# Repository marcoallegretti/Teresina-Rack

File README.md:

# Teresina-Rack

**Version 0.1.0-alpha0 — under engineering review; not fabricated or hardware-tested.** The current PCB is a 12-layer baseline with confirmed electrical, BOM, package and layout findings. It is not approved for production.

The goal is an open, self-fabricatable Daisy Patch SM-compatible Eurorack submodule: the same carrier interface and libDaisy application compatibility through a small Teresina firmware variant. Source compatibility and hardware behavior remain qualification targets. See [the firmware policy](docs/firmware-policy.md) and [production review](docs/production-review.md).

| Top | Bottom |
|---|---|
|  |  |

## Production target

**4 copper layers preferred; 6 acceptable if required; 8 the final fallback.** Evaluate in that order with new placement, BGA escape, timing, return-path and manufacturer review. Document the constraint and alternatives tried before increasing layer count. Twelve layers describe the existing file only and are outside the redesign target. See [the redesign plan](docs/redesign-plan.md).

Disposable four-layer MCU escape trials reached zero native clearance errors when six power-pad vias were filled/capped. The full board remains unrouted in those studies, and SDRAM escape at the inherited placement still fails. These results do not qualify a four-layer production design.

## Existing hardware

| Block | Baseline |
|---|---|
| Interface |68 × 40 mm, 40 through-hole mating pads; all 40 local pad geometries match official CAD |
| MCU |STM32H750IBK6, UFBGA176+25 balls, 480 MHz Cortex-M7 |
| RAM |IS42S32160F-6BLI prototype candidate, 64 MB, 3.3 V, 32-bit FMC; requires the Teresina refresh profile and hardware qualification |
| Flash |IS25LP064A, 8 MB QSPI |
| Codec |PCM3060, SAI1, I²C2 address 0x46 |
| Analog |TL074 audio, MCP6004 CV/gates, LM4040-10 V reference |
| Power |TPS62170 digital buck, LD1117 5 V stage; component selection/layout/budgets require correction |
| Files |209 schematic component references, 214 PCB footprints including five fiducials |

Manufacturer pin maps confirm the core/codec/analog signal assignments. 74 checked digital-net assignments agree with pinned libDaisy. Complete carrier fit, sequencing, analog performance and firmware execution still need first-article validation.

## Open compatibility findings

Official libDaisy v9.0.0 is the pinned firmware reference. Its stock refresh sweep is 168.35 ms against the proposed ISSI part's 64 ms requirement. An opt-in Teresina prototype now implements a conservative refresh profile and reviewed clock/init changes. Crossbuilds support a limited source-compatibility claim; stock binaries are unsupported and hardware tests remain unrun. See [the firmware decision](docs/firmware-policy.md) and [original retention check](docs/review/core-review/bounded-acceptance.md).

An [expanded memory-replacement search](docs/memory-replacement-search.md) found no datasheet-backed fix for unchanged firmware. Etron EM63B325BK is an unresolved catalogue lead; it has not been qualified or selected.

The review also confirms wrong ferrite/inductor/capacitor ordering data, crystal/diode footprint mismatches, CV amplifiers on the wrong supply, gate-output resistance differences and remote critical power/clock/decoupling loops. The earlier claims of an identical analog implementation and completed production validation are superseded by [the current findings](docs/production-review.md). Reviewed corrections are staged outside the checkout until the complete design can be synchronized.

## Validation

| Check | Baseline result and boundary |
|---|---|
| Native KiCad 10.0.7 DRC |0 errors, 0 unconnected, 414 warnings |
| Native ERC |3 power-pin conflicts, 250 warnings; unresolved |
| Native netlist→PCB |821 functional pad assignments agree; intentional NC aliases separately checked |
| Connectivity |200 routed nets connected; native zone-refill agreement |
| Copper hygiene |384 candidate findings; requires geometric review |
| SPICE |63 generated tests pass; ideal channel benches also executed; device/rail/tolerance coverage incomplete |
| EMC/thermal |Risk analyses executed; thermal budget incomplete; no compliance measurement |
| Fabrication export |34 Gerbers, PTH/NPTH drills, CPL; baseline only |

A clean native DRC does not resolve wrong ordered parts or prove stock-firmware retention, thermal safety, analog performance or carrier fit. See the full review for passed, failed and unrun checks.

## Development and fabrication

Use KiCad 10 for the project under `TeresinaRack/`. The configured cloud environment retains checksum-verified KiCad 10.0.7, ngspice 47, kicad-tools, KiCadRoutingTools and kicad-happy; reproducible setup/startup instructions are saved in environment settings. Interactive GUI editing and hardware programming were not validated in the headless environment.

Keep every routing operation's before/after evidence and run native DRC/refill, independent connectivity and copper hygiene before accepting it. Use the actual selected JLCPCB process, not an unrelated generic profile. Final fabrication requires an accepted stackup, explicit filled/capped-via process, corrected sourcing-complete BOM, CPL/assembly drawings, header dimensions and first-article plan. The current files and exports are not an approved order package.

```sh
kicad-cli pcb drc --format json -o drc.json TeresinaRack.kicad_pcb
kicad-cli sch erc --format json -o erc.json TeresinaRack.kicad_sch
```

Run from `TeresinaRack/` and inspect every report severity and unconnected item. Exit 0 alone does not establish a pass. Generated fabrication files belong in the ignored `fab/` directory.

## Repository layout

- `TeresinaRack/`: editable KiCad project, custom symbols and rules.
- `docs/production-review.md`: current evidence, blockers and review limits.
- `docs/redesign-plan.md`: requirements, 4 → 6 → 8 sequence and acceptance gates.
- `docs/review/`: inventory, calculations and independent subsystem evidence.
- `DESIGN.md`: historical working notes, superseded by the current review.
- `bom/`: baseline BOM working files; not approved production sourcing.

## Acknowledgements

- [Electro-Smith](https://electro-smith.com) — the Daisy platform, libDaisy, and the published
  Patch SM pinout/footprint that make a compatible open re-implementation possible.
- [kicad-happy](https://github.com/aklofas/kicad-happy) — schematic/PCB/EMC/SPICE analysis suite
  used for validation.

*This is an independent DIY project, not affiliated with or endorsed by Electro-Smith. "Daisy" and
"Patch SM" are their marks. Build at your own risk — check everything before powering your rack.*

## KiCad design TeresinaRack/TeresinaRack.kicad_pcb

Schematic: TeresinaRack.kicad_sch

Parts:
C1, C2, C3, C4, C5, C6, C7, C8, C9, C10, C16, C18, C19, C20, C21, C22, C23, C24, C25, C26, C29, C30, C31, C32, C39, C44, C51, C53, C57, C59, C61, C63, C102, C105, C112, C113, C140, C141, C142, C143, C204, C205, C206, C207: 100nF; C_0402_1005Metric; MPN CL05B104KO5NNNC; LCSC C1525
C11, C12, C27, C28: 4.7uF; C_0805_2012Metric; MPN CL21A475KAQNNNE; LCSC C1779
C13, C14, C50: 2.2uF; C_0603_1608Metric; MPN CL10A226MQ8NRNC; LCSC C59461
C15, C17, C48: 1uF; C_0402_1005Metric; MPN CL05A105KA5NQNC; LCSC C52923
C34, C35, C45, C47, C52, C54, C55, C60, C62: 10uF; C_0805_2012Metric; MPN CL21A106KAYNNNE; LCSC C15850
C36, C46: 22uF; C_0805_2012Metric; MPN CL21A226MOQNNNE; LCSC C98190
C37, C38, C120, C122, C123, C125: 18pF; C_0402_1005Metric; MPN 0402CG180J500NT; LCSC C1549
C56, C58: 22uF; C_1206_3216Metric; MPN CL31A226KAHNNNE; LCSC C12891
C100, C103: 2.2uF; C_0805_2012Metric; MPN CL21A226MAQNNNE; LCSC C45783
C101, C104, C126, C127, C128, C129, C130, C131, C132, C133: 220pF; C_0402_1005Metric; MPN 0402B221K500NT; LCSC C1530
C121, C124: 100pF; C_0402_1005Metric; MPN 0402CG101J500NT; LCSC C1546
C134, C135, C136, C137, C138, C139: 1nF; C_0402_1005Metric; MPN 0402B102K500NT; LCSC C1523
C201: 2.2uF; C_0603_1608Metric; MPN CL10A225KO8NNNC; LCSC C23630
C202: 100nF; C_0402_1005Metric
C203: 10uF; C_0805_2012Metric
D1, D2, D5: NSR1020; D_SOD-923; MPN NSR1020MW2T1G; LCSC C116953
D3: LED_USER; LED_0603_1608Metric; MPN XL-1608SYGC-06; LCSC C965805
D4: LED_PWR; LED_0603_1608Metric; MPN KT-0603R; LCSC C2286
FB1, FB2: 600R@100MHz; L_0603_1608Metric; MPN MCR03EZPFX3600; LCSC C559338
FB3, FB5, FB7, FB8: 600R@100MHz; L_0805_2012Metric; MPN CR0805FR600P05Z; LCSC C175716
FB9: 600R@100MHz; L_0805_2012Metric
J3: USB_Micro-B; USB_Micro-B_Amphenol_10118194-0001LF_Horizontal; MPN 10118194-0001LF; LCSC C132563
J4: SWD; PinHeader_2x05_P1.27mm_Vertical_SMD; MPN SWD062R08E8T; LCSC C5151848
J5: PATCH_SM_EDGE; DAISY_PATCH_SM
L1: 2.2uH; L_1210_3225Metric; MPN NLCV32T-220K-EF; LCSC C250233
Q1, Q2: MMBT3904; SOT-23; MPN MMBT3904(RANGE:100-300); LCSC C20526
R1, R2: 4.7k; R_0402_1005Metric; MPN 0402WGF4701TCE; LCSC C25900
R3, R4, R21: 10k; R_0402_1005Metric; MPN 0402WGF1002TCE; LCSC C25744
R11: 5.1R; R_0402_1005Metric; MPN 0402WGF510KTCE; LCSC C25128
R12: 47k; R_0402_1005Metric; MPN 0402WGF4702TCE; LCSC C25792
R13: 15k; R_0402_1005Metric; MPN 0402WGF1502TCE; LCSC C25756
R14, R15: 1k; R_0402_1005Metric; MPN 0402WGF1001TCE; LCSC C11702
R100, R103, R111, R114, R118, R121: 66K5; R_0402_1005Metric; MPN RC0402FR-0766K5L; LCSC C327329
R101, R104: 15K; R_0402_1005Metric; MPN 0402WGF1502TCE; LCSC C25756
R102, R105, R148, R149, R150, R151, R152, R153, R162, R163, R202, R203: 1K; R_0402_1005Metric; MPN 0402WGF1001TCE; LCSC C11702
R110, R113, R117, R120: 18K; R_0402_1005Metric; MPN 0402WGF1802TCE; LCSC C25762
R112, R115, R119, R122: 39K; R_0402_1005Metric; MPN 0402WGF3902TCE; LCSC C25783
R116, R123, R158, R159: 100R; R_0402_1005Metric; MPN RC0402FR-07100RL; LCSC C106232
R124, R125, R126, R127, R128, R129, R130, R131, R160, R161, R164, R165: 100K; R_0402_1005Metric; MPN 0402WGF1003TCE; LCSC C25741
R132, R133, R134, R135, R136, R137, R138, R139: 200K; R_0402_1005Metric; MPN 0402WGF2003TCE; LCSC C25764
R140, R141, R142, R143, R144, R145, R146, R147: 33K; R_0402_1005Metric; MPN 0402WGF3302TCE; LCSC C25779
R154, R155: 120K; R_0402_1005Metric; MPN 0402WGF1203TCE; LCSC C25750
R156, R157: 62K; R_0402_1005Metric; MPN FRC0402F6202TS; LCSC C2909375
R166, R167: 1M; R_0402_1005Metric; MPN 0402WGF1004TCE; LCSC C26083
R168, R169: 10K; R_0402_1005Metric; MPN 0402WGF1002TCE; LCSC C72443
R170: 2K; R_0402_1005Metric; MPN 0402WGF2001TCE; LCSC C4109
R201: 4K7; R_0402_1005Metric; MPN 0402WGF4701TCE; LCSC C25900
SW1: RESET; SW_Push_1P1T_NO_CK_KMR2; MPN KMR231NGLFS; LCSC C72443
SW2: BOOT; SW_Push_1P1T_NO_CK_KMR2; MPN KMR231NGLFS; LCSC C72443
U1: STM32H750IBK6; UFBGA-201_10x10mm_Layout15x15_P0.65mm; MPN STM32H750IBK6; LCSC C730200
U2: IS25LP064A; SOIC-8_5.3x5.3mm_P1.27mm; MPN IS25LP064A-JBLE; LCSC C2841348
U3: IS42S32160F-6BLI; BGA-90_8.0x13.0mm_Layout2x3x15_P0.8mm; MPN IS42S32160F-6BLI; LCSC C1348852
U4: PCM3060; TSSOP-28_4.4x9.7mm_P0.65mm; MPN PCM3060PWR; LCSC C2651841
U6: TPS62170DSGR; Texas_DSG0008A_WSON-8-1EP_2x2mm_P0.5mm_EP0.9x1.6mm; MPN TPS62170DSGR; LCSC C124041
U7: LD1117S50; SOT-223-3_TabPin2; MPN LD1117S50CTR; LCSC C81157
U8: USBLC6-2SC6; SOT-23-6; MPN USBLC6-2SC6; LCSC C7519
U12: TL074; SOIC-14_3.9x8.7mm_P1.27mm; MPN TL074IDT; LCSC C107644
U13, U14, U15: MCP6004; SOIC-14_3.9x8.7mm_P1.27mm; MPN MCP6004T-I/SL; LCSC C7378
U16: LM4040DBZ-10; SOT-23; MPN LM4040C10IDBZR; LCSC C201738
Y1: 16MHz; Crystal_SMD_3215-2Pin_3.2x1.5mm; MPN X322516MLB4SI; LCSC C13738

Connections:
+3V3: C1.1, C2.1, C3.1, C4.1, C5.1, C6.1, C7.1, C8.1, C9.1, C10.1, C11.1, C12.1, C18.1, C19.1, C20.1, C21.1, C22.1, C23.1, C24.1, C25.1, C26.1, C27.1, C28.1, C29.1, C30.1, C32.1, C36.1, C46.1, C51.1, C52.1, C204.1, C205.1, C206.1, C207.1, FB5.1, J4.1, J5.A10 (+3V3), L1.2, R1.1, R2.1, R3.1, R12.1, R15.1, R21.2, R160.1, R168.1, R169.1, SW2.2, U1.C1 (VBAT), U1.C5 (VDD), U1.C6 (PDR_ON), U1.C7 (VDD), U1.C8 (VDD), U1.C9 (VDD), U1.F3 (VDD), U1.G3 (VDD), U1.G13 (VDD), U1.H13 (VDD33_USB), U1.J12 (VDD), U1.J13 (VDD), U1.K4 (VDD), U1.N8 (VDD), U1.N9 (VDD), U1.N10 (VDD), U2.8 (VCC), U3.A7 (VDD), U3.B2 (VDDQ), U3.B7 (VDDQ), U3.C9 (VDDQ), U3.D9 (VDDQ), U3.E1 (VDDQ), U3.F9 (VDD), U3.L1 (VDDQ), U3.L7 (VDD), U3.M9 (VDDQ), U3.N9 (VDDQ), U3.P2 (VDDQ), U3.P7 (VDDQ), U3.R7 (VDD), U4.7 (V_{DD}), U4.15 (~RST), U6.6 (VOS)
+3V3A: C15.1, C16.1, C17.1, C31.1, C34.1, C53.1, C54.1, C62.1, FB1.2, FB5.2, U1.P1 (VREF+), U1.R1 (VDDA)
+5V: C60.1, C61.1, C141.1, C142.1, C143.1, FB8.2, FB9.1, J5.A6 (+5V), U13.4 (V+), U14.4 (V+), U15.4 (V+)
+5VA: C202.1, C203.1, FB9.2, U4.24 (V_{CC})
+12V: C56.1, C57.1, C112.1, D1.1 (K), D5.1 (K), FB3.1, FB7.1, U12.4 (V+)
-12V: C58.1, C59.1, C113.1, D2.2 (A), R170.2, U12.11 (V-)
ADCJACK_9: J5.A2 (UART_RX), R148.1
ADCJACK_10: J5.A3 (UART_TX), R149.1
ADCJACK_11: J5.D9 (SPI_MOSI), R150.1
ADCJACK_12: J5.D8 (SPI_MISO), R151.1
ADC_9: C134.1, R148.2, U1.N2 (PA1)
ADC_10: C135.1, R149.2, U1.N3 (PA0)
ADC_11: C136.1, R150.2, U1.M5 (PC3_C)
ADC_12: C137.1, R151.2, U1.M4 (PC2_C)
AUDIO_OUT_L: J5.B2 (AUDIO_OUT_L), R116.2
AUDIO_OUT_R: J5.B1 (AUDIO_OUT_R), R123.2
A_IN: C47.1, C48.1, R11.2
A_OUT: C50.1, FB1.1
BOOT0: C201.1, R4.1, R201.2, SW2.1, U1.D6 (BOOT0)
BOOT_FLASH: R201.1, U1.K15 (PG3)
CODEC_IN_L: R105.2, U4.25 (V_{IN}L)
CODEC_IN_R: R102.2, U4.26 (V_{IN}R)
CODEC_OUT_L+: R110.1, U4.20 (V_{OUT}L+)
CODEC_OUT_L-: R113.1, U4.19 (V_{OUT}L-)
CODEC_OUT_R+: R117.1, U4.18 (V_{OUT}R+)
CODEC_OUT_R-: R120.1, U4.17 (V_{OUT}R-)
CODEC_VCOM: C55.1, C102.1, C105.1, U4.21 (V_{COM}), U12.10 (+), U12.12 (+)
CVJACK_1: J5.C5 (CV1), R124.1
CVJACK_2: J5.C4 (CV2), R125.1
CVJACK_3: J5.C3 (CV3), R126.1
CVJACK_4: J5.C2 (CV4), R127.1
CVJACK_5: J5.C6 (CV5), R128.1
CVJACK_6: J5.C7 (CV6), R129.1
CVJACK_7: J5.C8 (CV7), R130.1
CVJACK_8: J5.C9 (CV8), R131.1
CVOUT_1: J5.C10 (CV_OUT_1), R158.2
CVOUT_1_O: R156.2, R158.1, U15.1
CVOUT_2: J5.C1 (CV_OUT_2), R159.2
CVOUT_2_O: R157.2, R159.1, U15.7
CVO_FB_1: R154.1, R156.1, U15.2 (-)
CVO_FB_2: R155.1, R157.1, U15.6 (-)
CVO_FILT_1: C138.1, R152.2, U15.3 (+)
CVO_FILT_2: C139.1, R153.2, U15.5 (+)
CV_1: C126.1, R140.1, U1.R2 (PA3), U13.1
CV_2: C127.1, R141.1, U1.P3 (PA6), U13.7
CV_3: C128.1, R142.1, U1.P2 (PA2), U13.8
CV_4: C129.1, R143.1, U1.R3 (PA7), U13.14
CV_5: C130.1, R144.1, U1.R4 (PB1), U14.1
CV_6: C131.1, R145.1, U1.N5 (PC4), U14.7
CV_7: C132.1, R146.1, U1.M2 (PC0), U14.8
CV_8: C133.1, R147.1, U1.M3 (PC1), U14.14
CV_OUT_1: R152.1, U1.N4 (PA4)
CV_OUT_2: R153.1, U1.P4 (PA5)
FB_BK: R12.2, R13.1, U6.5 (FB)
FMC_A0: U1.E2 (PF0), U3.G8 (A0)
FMC_A1: U1.H3 (PF1), U3.G9 (A1)
FMC_A2: U1.H2 (PF2), U3.F7 (A2)
FMC_A3: U1.J2 (PF3), U3.F3 (A3)
FMC_A4: U1.J3 (PF4), U3.G1 (A4)
FMC_A5: U1.K3 (PF5), U3.G2 (A5)
FMC_A6: U1.P6 (PF12), U3.G3 (A6)
FMC_A7: U1.N6 (PF13), U3.H1 (A7)
FMC_A8: U1.R7 (PF14), U3.H2 (A8)
FMC_A9: U1.P7 (PF15), U3.J3 (A9)
FMC_A10: U1.N7 (PG0), U3.G7 (A10)
FMC_A11: U1.M7 (PG1), U3.H9 (A11)
FMC_A12: U1.L15 (PG2), U3.H3 (A12)
FMC_BA0: U1.K14 (PG4), U3.J7 (BA0)
FMC_BA1: U1.K13 (PG5), U3.H8 (BA1)
FMC_D0: U1.M14 (PD14), U3.R8 (DQ0)
FMC_D1: U1.L14 (PD15), U3.N7 (DQ1)
FMC_D2: U1.B12 (PD0), U3.R9 (DQ2)
FMC_D3: U1.C12 (PD1), U3.N8 (DQ3)
FMC_D4: U1.R8 (PE7), U3.P9 (DQ4)
FMC_D5: U1.P8 (PE8), U3.M8 (DQ5)
FMC_D6: U1.P9 (PE9), U3.M7 (DQ6)
FMC_D7: U1.R9 (PE10), U3.L8 (DQ7)
FMC_D8: U1.P10 (PE11), U3.L2 (DQ8)
FMC_D9: U1.R10 (PE12), U3.M3 (DQ9)
FMC_D10: U1.N11 (PE13), U3.M2 (DQ10)
FMC_D11: U1.P11 (PE14), U3.P1 (DQ11)
FMC_D12: U1.R11 (PE15), U3.N2 (DQ12)
FMC_D13: U1.P15 (PD8), U3.R1 (DQ13)
FMC_D14: U1.P14 (PD9), U3.N3 (DQ14)
FMC_D15: U1.N15 (PD10), U3.R2 (DQ15)
FMC_D16: U1.M12 (PH8), U3.E8 (DQ16)
FMC_D17: U1.M13 (PH9), U3.D7 (DQ17)
FMC_D18: U1.L13 (PH10), U3.D8 (DQ18)
FMC_D19: U1.L12 (PH11), U3.B9 (DQ19)
FMC_D20: U1.K12 (PH12), U3.C8 (DQ20)
FMC_D21: U1.E12 (PH13), U3.A9 (DQ21)
FMC_D22: U1.E13 (PH14), U3.C7 (DQ22)
FMC_D23: U1.D13 (PH15), U3.A8 (DQ23)
FMC_D24: U1.E14 (PI0), U3.A2 (DQ24)
FMC_D25: U1.D14 (PI1), U3.C3 (DQ25)
FMC_D26: U1.C14 (PI2), U3.A1 (DQ26)
FMC_D27: U1.C13 (PI3), U3.C2 (DQ27)
FMC_D28: U1.C3 (PI6), U3.B1 (DQ28)
FMC_D29: U1.C2 (PI7), U3.D2 (DQ29)
FMC_D30: U1.D3 (PI9), U3.D3 (DQ30)
FMC_D31: U1.E3 (PI10), U3.E2 (DQ31)
FMC_NBL0: U1.A4 (PE0), U3.K9 (DQM0)
FMC_NBL1: U1.A3 (PE1), U3.K1 (DQM1)
FMC_NBL2: U1.D4 (PI4), U3.F8 (DQM2)
FMC_NBL3: U1.C4 (PI5), U3.F2 (DQM3)
FMC_SDCKE0: U1.F4 (PH2), U3.J2 (CKE)
FMC_SDCLK: U1.H14 (PG8), U3.J1 (CLK)
FMC_SDNCAS: U1.B7 (PG15), U3.K7 (CAS#)
FMC_SDNE0: U1.G4 (PH3), U3.J8 (CS#)
FMC_SDNRAS: U1.R6 (PF11), U3.J9 (RAS#)
FMC_SDNWE: U1.J4 (PH5), U3.K8 (WE#)
GATEJACK_1: J5.B10 (GATE_IN_1), R164.1
GATEJACK_2: J5.B9 (GATE_IN_2), R165.1
GATEOUT_1: J5.B5 (GATE_OUT_1), R162.2
GATEOUT_1_O: R162.1, U15.8
GATEOUT_2: J5.B6 (GATE_OUT_2), R163.2
GATEOUT_2_O: R163.1, U15.14
GATE_IN_1: Q1.3 (C), R168.2, R202.1
GATE_IN_1_MCU: R202.2, U1.A8 (PG13)
GATE_IN_2: Q2.3 (C), R169.2, R203.1
GATE_IN_2_MCU: R203.2, U1.A7 (PG14)
GATE_OUT_1: U1.E1 (PC14), U15.10 (+)
GATE_OUT_2: U1.D1 (PC13), U15.12 (+)
GBASE_1: Q1.1 (B), R164.2, R166.1
GBASE_2: Q2.1 (B), R165.2, R167.1
GND: C1.2, C2.2, C3.2, C4.2, C5.2, C6.2, C7.2, C8.2, C9.2, C10.2, C11.2, C12.2, C13.2, C14.2, C15.2, C16.2, C17.2, C18.2, C19.2, C20.2, C21.2, C22.2, C23.2, C24.2, C25.2, C26.2, C27.2, C28.2, C29.2, C30.2, C31.2, C32.2, C34.2, C35.2, C36.2, C37.2, C38.2, C39.2, C44.2, C45.2, C46.2, C47.2, C48.2, C50.2, C51.2, C52.2, C53.2, C54.2, C55.2, C56.2, C57.2, C58.2, C59.2, C60.2, C61.2, C62.2, C63.2, C102.2, C105.2, C112.2, C113.2, C122.2, C125.2, C134.2, C135.2, C136.2, C137.2, C138.2, C139.2, C140.2, C141.2, C142.2, C143.2, C201.2, C202.2, C203.2, C204.2, C205.2, C206.2, C207.2, D3.1 (K), D4.1 (K), J3.5 (GND), J3.SH (Shield), J4.3, J4.5, J4.9, J5.A4 (GND), J5.A7 (GND), Q1.2 (E), Q2.2 (E), R4.2, R13.2, R115.2, R122.2, R154.2, R155.2, R161.2, R166.2, R167.2, SW1.2, U1.D5 (VSS), U1.D7 (VSS), U1.D8 (VSS), U1.D9 (VSS), U1.F2 (VSS), U1.F6 (VSS), U1.F7 (VSS), U1.F8 (VSS), U1.F9 (VSS), U1.F10 (VSS), U1.F12 (VSS), U1.G2 (VSS), U1.G6 (VSS), U1.G7 (VSS), U1.G8 (VSS), U1.G9 (VSS), U1.G10 (VSS), U1.G12 (VSS), U1.H6 (VSS), U1.H7 (VSS), U1.H8 (VSS), U1.H9 (VSS), U1.H10 (VSS), U1.H12 (VSS), U1.J6 (VSS), U1.J7 (VSS), U1.J8 (VSS), U1.J9 (VSS), U1.J10 (VSS), U1.K6 (VSS), U1.K7 (VSS), U1.K8 (VSS), U1.K9 (VSS), U1.K10 (VSS), U1.L4 (VSS), U1.M1 (VSSA), U1.M8 (VSS), U1.M9 (VSS), U1.N1 (VREF-), U2.4 (GND), U3.A3 (VSS), U3.B3 (VSSQ), U3.B8 (VSSQ), U3.C1 (VSSQ), U3.D1 (VSSQ), U3.E9 (VSSQ), U3.F1 (VSS), U3.L3 (VSS), U3.L9 (VSSQ), U3.M1 (VSSQ), U3.N1 (VSSQ), U3.P3 (VSSQ), U3.P8 (VSSQ), U3.R3 (VSS), U4.8 (DGND), U4.16 (SGND), U4.22 (AGND2), U4.23 (AGND1), U4.27 (~MS/AD/IFMD), U4.28 (MODE), U6.1 (PGND), U6.4 (AGND), U6.9 (PAD), U7.1 (GND), U8.2 (GND), U13.3 (+), U13.5 (+), U13.10 (+), U13.11 (V-), U13.12 (+), U14.3 (+), U14.5 (+), U14.10 (+), U14.11 (V-), U14.12 (+), U15.11 (V-), U16.1 (K)
I2C1_SCL: J5.B7 (I2C1_SCL), U1.A5 (PB8)
I2C1_SDA: J5.B8 (I2C1_SDA), U1.B4 (PB9)
I2C2_SCL: R2.2, U1.R12 (PB10), U4.1 (MC/SCL/FMT)
I2C2_SDA: R1.2, U1.R13 (PB11), U4.2 (MD/SDA/DEMP)
INPUT_+12V: D1.2 (A), J5.A5 (+12V)
INPUT_-12V: D2.1 (K), J5.A1 (-12V)
INPUT_AUDIO_LEFT: C103.1, J5.B4 (AUDIO_IN_L)
INPUT_AUDIO_RIGHT: C100.1, J5.B3 (AUDIO_IN_R)
JTDI: J4.8, U1.A13 (PA15)
LD_IN: C63.1, FB7.2, U7.3 (VI)
LD_OUT: FB8.1, U7.2 (VO)
LED_A: D3.2 (A), R14.2
LED_USER: R14.1, U1.G15 (PC7)
LINL_M: C104.1, R103.2, R104.1, U12.13 (-)
LINL_O: C104.2, R104.2, R105.1, U12.14
NC_U3_E3: U3.E3 (NC)
NC_U3_E7: U3.E7 (NC)
NC_U3_H7: U3.H7 (NC)
NC_U3_K2: U3.K2 (NC)
NC_U3_K3: U3.K3 (NC)
NRST: C39.1, J4.10, R3.2, SW1.1, U1.J1 (NRST)
N_LINA: C103.2, R103.1
N_OLA: C121.1, R110.2, R111.1, R112.2
N_OLB: C121.2, R113.2, R114.1, R115.1
N_ORA: C124.1, R117.2, R118.1, R119.2
N_ORB: C124.2, R120.2, R121.1, R122.1
N_RINA: C100.2, R100.1
OL_INV: C120.2, R111.2, U12.6 (-)
OL_NINV: C122.1, R114.2, U12.5 (+)
OL_OUT: C120.1, R112.1, R116.1, U12.7
OR_INV: C123.2, R118.2, U12.2 (-)
OR_NINV: C125.1, R121.2, U12.3 (+)
OR_OUT: C123.1, R119.1, R123.1, U12.1
OSC_IN: C37.1, U1.G1 (PH0), Y1.1
OSC_OUT: C38.1, U1.H1, Y1.2
PWR_A: D4.2 (A), R15.2
QSPI_CLK: U1.L1 (PF10), U2.6 (CLK)
QSPI_IO0: U1.L3 (PF8), U2.5 (IO0)
QSPI_IO1: U1.L2 (PF9), U2.2 (IO1)
QSPI_IO2: U1.K1 (PF7), U2.3 (IO2)
QSPI_IO3: U1.K2 (PF6), U2.7 (IO3)
QSPI_NCS: R21.1, U1.J15 (PG6), U2.1 (CS#)
RINR_M: C101.1, R100.2, R101.1, U12.9 (-)
RINR_O: C101.2, R101.2, R102.1, U12.8
SAI1_FS: U1.B1 (PE4), U4.4 (LRCK1), U4.11 (LRCK2)
SAI1_MCLK: U1.A2 (PE2), U4.6 (SCKI1), U4.9 (SCKI2)
SAI1_SCK: U1.B2 (PE5), U4.5 (BCK1), U4.10 (BCK2)
SAI1_SDA: U1.B3 (PE6), U4.3 (DOUT)
SAI1_SDB: U1.A1 (PE3), U4.12 (DIN)
SDMMC1_CK: J5.D6 (SDMMC_CK), U1.A12 (PC12)
SDMMC1_CMD: J5.D7 (SDMMC_CMD), U1.D12 (PD2)
SDMMC1_D0: J5.D5 (SDMMC_D0), U1.G14 (PC8)
SDMMC1_D1: J5.D4 (SDMMC_D1), U1.F14 (PC9)
SDMMC1_D2: J5.D3 (SDMMC_D2), U1.B14 (PC10)
SDMMC1_D3: J5.D2 (SDMMC_D3), U1.B13 (PC11)
SPI2_CS: J5.D1 (SPI_NSS), U1.A9 (PB4)
SPI2_SCK: J5.D10 (SPI_SCK), U1.D11 (PD3)
SUM_1: C126.2, R124.2, R132.2, R140.2, U13.2 (-)
SUM_2: C127.2, R125.2, R133.2, R141.2, U13.6 (-)
SUM_3: C128.2, R126.2, R134.2, R142.2, U13.9 (-)
SUM_4: C129.2, R127.2, R135.2, R143.2, U13.13 (-)
SUM_5: C130.2, R128.2, R136.2, R144.2, U14.2 (-)
SUM_6: C131.2, R129.2, R137.2, R145.2, U14.6 (-)
SUM_7: C132.2, R130.2, R138.2, R146.2, U14.9 (-)
SUM_8: C133.2, R131.2, R139.2, R147.2, U14.13 (-)
SWCLK: J4.4, U1.A14
SWDIO: J4.2, U1.A15 (PA13)
SWO: J4.6, U1.A10 (PB3)
SW_BK: L1.1, U6.7 (SW)
UNREG: C35.1, C44.1, FB2.1, R11.1
USB_DM: J5.A8 (USB_DM), U1.R14 (PB14)
USB_DP: J5.A9 (USB_DP), U1.R15 (PB15)
USB_FS_DM: J3.2 (D-), U1.C15 (PA11), U8.1 (I/O1), U8.6 (I/O1)
USB_FS_DP: J3.3 (D+), U1.B15 (PA12), U8.3 (I/O2), U8.4 (I/O2)
VBUS: D5.2 (A), J3.1 (VBUS), U8.5 (VBUS)
VCAP: C13.1, C14.1, U1.F13 (VCAP), U1.M10 (VCAP)
VIN_BK: C45.1, FB2.2, FB3.2, U6.2 (VIN), U6.3 (EN)
VREF_N10: C140.1, R132.1, R133.1, R134.1, R135.1, R136.1, R137.1, R138.1, R139.1, R170.1, U16.2 (A)
VTH: R160.2, R161.1, U15.9 (-), U15.13 (-)

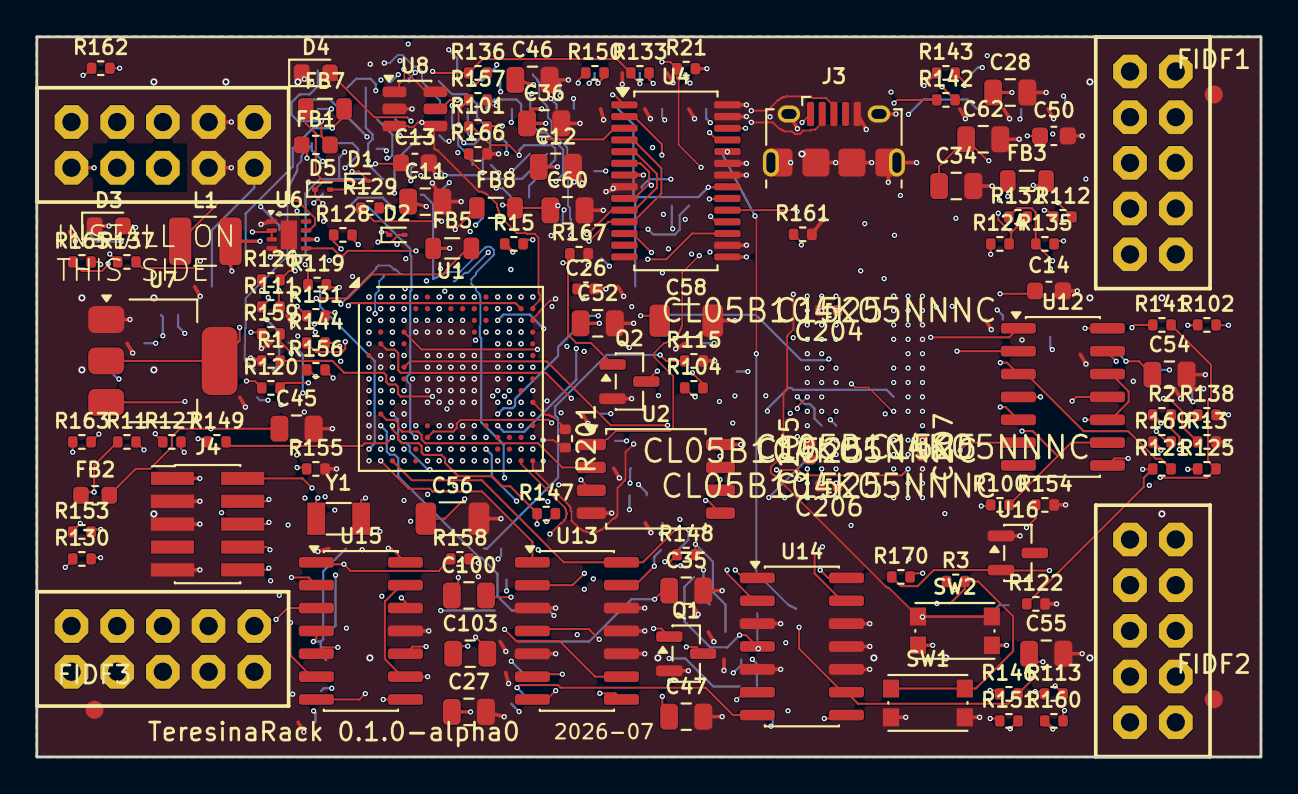
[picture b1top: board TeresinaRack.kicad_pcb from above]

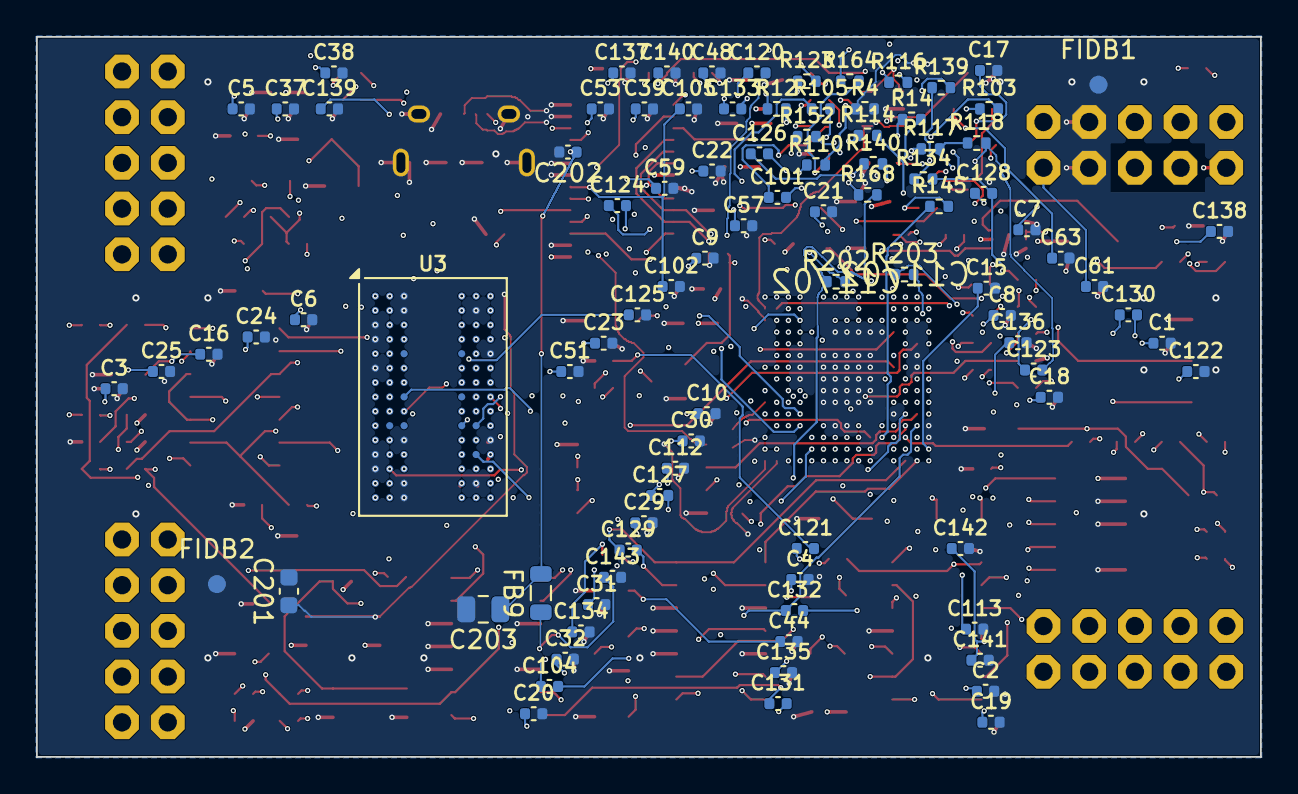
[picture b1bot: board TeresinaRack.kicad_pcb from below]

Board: 12 copper layers, 68.0 x 40.0 mm, 214 parts (93 on the bottom side), 200 nets.

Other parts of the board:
FIDB1, FIDB2: Fiducial_1mm_Mask2mm
FIDF1, FIDF2, FIDF3: Fiducial_1mm_Mask2mm

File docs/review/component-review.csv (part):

reference,value,mpn,lcsc,footprint,side,x_mm,y_mm,datasheet,review_status,circuit_review_group,connected_nets,placement_requirement
C1,100nF,CL05B104KO5NNNC,C1525,Capacitor_SMD:C_0402_1005Metric,B.Cu,5.488,17.016,,pinout/dimensions/sourcing review required,Power distribution; pin-level owner pending,+3V3;GND,Place by datasheet pin/loop requirements after source review; existing coordinates are not approved
C10,100nF,CL05B104KO5NNNC,C1525,Capacitor_SMD:C_0402_1005Metric,B.Cu,30.775,20.931,,pinout/dimensions/sourcing review required,Power distribution; pin-level owner pending,+3V3;GND,Place by datasheet pin/loop requirements after source review; existing coordinates are not approved
C100,2.2uF,CL21A226MAQNNNE,C45783,Capacitor_SMD:C_0805_2012Metric,F.Cu,24,31.03,,pinout/dimensions/sourcing review required,Audio/codec; pin-level owner pending,INPUT_AUDIO_RIGHT;N_RINA,Place by datasheet pin/loop requirements after source review; existing coordinates are not approved
C101,220pF,0402B221K500NT,C1530,Capacitor_SMD:C_0402_1005Metric,B.Cu,26.86,8.917,,pinout/dimensions/sourcing review required,Power distribution; pin-level owner pending,RINR_M;RINR_O,Place by datasheet pin/loop requirements after source review; existing coordinates are not approved
C102,100nF,CL05B104KO5NNNC,C1525,Capacitor_SMD:C_0402_1005Metric,B.Cu,32.759,13.867,,pinout/dimensions/sourcing review required,Audio/codec; pin-level owner pending,CODEC_VCOM;GND,Place by datasheet pin/loop requirements after source review; existing coordinates are not approved
C103,2.2uF,CL21A226MAQNNNE,C45783,Capacitor_SMD:C_0805_2012Metric,F.Cu,24.074,34.265,,pinout/dimensions/sourcing review required,Audio/codec; pin-level owner pending,INPUT_AUDIO_LEFT;N_LINA,Place by datasheet pin/loop requirements after source review; existing coordinates are not approved
C104,220pF,0402B221K500NT,C1530,Capacitor_SMD:C_0402_1005Metric,B.Cu,39.525,36.086,,pinout/dimensions/sourcing review required,Power distribution; pin-level owner pending,LINL_M;LINL_O,Place by datasheet pin/loop requirements after source review; existing coordinates are not approved
C105,100nF,CL05B104KO5NNNC,C1525,Capacitor_SMD:C_0402_1005Metric,B.Cu,31.8,4,,pinout/dimensions/sourcing review required,Audio/codec; pin-level owner pending,CODEC_VCOM;GND,Place by datasheet pin/loop requirements after source review; existing coordinates are not approved
C11,4.7uF,CL21A475KAQNNNE,C1779,Capacitor_SMD:C_0805_2012Metric,F.Cu,21.574,9.15,,pinout/dimensions/sourcing review required,Power distribution; pin-level owner pending,+3V3;GND,Place by datasheet pin/loop requirements after source review; existing coordinates are not approved
C112,100nF,CL05B104KO5NNNC,C1525,Capacitor_SMD:C_0402_1005Metric,B.Cu,32.525,23.962,,pinout/dimensions/sourcing review required,Power distribution; pin-level owner pending,+12V;GND,Place by datasheet pin/loop requirements after source review; existing coordinates are not approved
C113,100nF,CL05B104KO5NNNC,C1525,Capacitor_SMD:C_0402_1005Metric,B.Cu,15.903,32.904,,pinout/dimensions/sourcing review required,Power distribution; pin-level owner pending,-12V;GND,Place by datasheet pin/loop requirements after source review; existing coordinates are not approved
C12,4.7uF,CL21A475KAQNNNE,C1779,Capacitor_SMD:C_0805_2012Metric,F.Cu,28.827,7.219,,pinout/dimensions/sourcing review required,Power distribution; pin-level owner pending,+3V3;GND,Place by datasheet pin/loop requirements after source review; existing coordinates are not approved
C120,18pF,0402CG180J500NT,C1549,Capacitor_SMD:C_0402_1005Metric,B.Cu,28,2,,pinout/dimensions/sourcing review required,Power distribution; pin-level owner pending,OL_INV;OL_OUT,Place by datasheet pin/loop requirements after source review; existing coordinates are not approved
C121,100pF,0402CG101J500NT,C1546,Capacitor_SMD:C_0402_1005Metric,B.Cu,25.306,28.423,,pinout/dimensions/sourcing review required,Audio/codec; pin-level owner pending,N_OLA;N_OLB,Place by datasheet pin/loop requirements after source review; existing coordinates are not approved
C122,18pF,0402CG180J500NT,C1549,Capacitor_SMD:C_0402_1005Metric,B.Cu,3.611,18.591,,pinout/dimensions/sourcing review required,Power distribution; pin-level owner pending,GND;OL_NINV,Place by datasheet pin/loop requirements after source review; existing coordinates are not approved
C123,18pF,0402CG180J500NT,C1549,Capacitor_SMD:C_0402_1005Metric,B.Cu,12.625,18.506,,pinout/dimensions/sourcing review required,Power distribution; pin-level owner pending,OR_INV;OR_OUT,Place by datasheet pin/loop requirements after source review; existing coordinates are not approved
C124,100pF,0402CG101J500NT,C1546,Capacitor_SMD:C_0402_1005Metric,B.Cu,35.753,9.37,,pinout/dimensions/sourcing review required,Audio/codec; pin-level owner pending,N_ORA;N_ORB,Place by datasheet pin/loop requirements after source review; existing coordinates are not approved
C125,18pF,0402CG180J500NT,C1549,Capacitor_SMD:C_0402_1005Metric,B.Cu,34.636,15.442,,pinout/dimensions/sourcing review required,Power distribution; pin-level owner pending,GND;OR_NINV,Place by datasheet pin/loop requirements after source review; existing coordinates are not approved
C126,220pF,0402B221K500NT,C1530,Capacitor_SMD:C_0402_1005Metric,B.Cu,27.86,6.497,,pinout/dimensions/sourcing review required,CV/gate analog; channel owner pending,CV_1;SUM_1,Place by datasheet pin/loop requirements after source review; existing coordinates are not approved
C127,220pF,0402B221K500NT,C1530,Capacitor_SMD:C_0402_1005Metric,B.Cu,33.4,25.477,,pinout/dimensions/sourcing review required,CV/gate analog; channel owner pending,CV_2;SUM_2,Place by datasheet pin/loop requirements after source review; existing coordinates are not approved
C128,220pF,0402B221K500NT,C1530,Capacitor_SMD:C_0402_1005Metric,B.Cu,15.408,8.692,,pinout/dimensions/sourcing review required,CV/gate analog; channel owner pending,CV_3;SUM_3,Place by datasheet pin/loop requirements after source review; existing coordinates are not approved
C129,220pF,0402B221K500NT,C1530,Capacitor_SMD:C_0402_1005Metric,B.Cu,35.15,28.509,,pinout/dimensions/sourcing review required,CV/gate analog; channel owner pending,CV_4;SUM_4,Place by datasheet pin/loop requirements after source review; existing coordinates are not approved
C13,2.2uF,CL10A226MQ8NRNC,C59461,Capacitor_SMD:C_0603_1608Metric,F.Cu,21,7,,pinout/dimensions/sourcing review required,Power distribution; pin-level owner pending,GND;VCAP,Place by datasheet pin/loop requirements after source review; existing coordinates are not approved
C130,220pF,0402B221K500NT,C1530,Capacitor_SMD:C_0402_1005Metric,B.Cu,7.364,15.442,,pinout/dimensions/sourcing review required,CV/gate analog; channel owner pending,CV_5;SUM_5,Place by datasheet pin/loop requirements after source review; existing coordinates are not approved
C131,220pF,0402B221K500NT,C1530,Capacitor_SMD:C_0402_1005Metric,B.Cu,26.826,37.04,,pinout/dimensions/sourcing review required,CV/gate analog; channel owner pending,CV_6;SUM_6,Place by datasheet pin/loop requirements after source review; existing coordinates are not approved
C132,220pF,0402B221K500NT,C1530,Capacitor_SMD:C_0402_1005Metric,B.Cu,25.914,31.87,,pinout/dimensions/sourcing review required,CV/gate analog; channel owner pending,CV_7;SUM_7,Place by datasheet pin/loop requirements after source review; existing coordinates are not approved
C133,220pF,0402B221K500NT,C1530,Capacitor_SMD:C_0402_1005Metric,B.Cu,29.35,4,,pinout/dimensions/sourcing review required,CV/gate analog; channel owner pending,CV_8;SUM_8,Place by datasheet pin/loop requirements after source review; existing coordinates are not approved
C134,1nF,0402B102K500NT,C1523,Capacitor_SMD:C_0402_1005Metric,B.Cu,37.775,33.055,,pinout/dimensions/sourcing review required,Auxiliary ADC,ADC_9;GND,Place by datasheet pin/loop requirements after source review; existing coordinates are not approved
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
